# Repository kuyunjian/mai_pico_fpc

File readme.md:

.

.

.

.

.

# 1. 开源外壳适配的背板部分
.

.

.

.

.

.

.

.

.

.

## 这两个文件参考价格40-50元

## 安装指南如图
.

.

.

.

.

.

.

.

.

.

## t型螺母在匹配的方向可以直接盖到铝型材里
## 螺丝用m4L16 L17 L18都可以

## 还可以买M4L11或者L12或者L13的沉头螺丝（或者非沉头螺丝两个）安装侧边提手，有预留孔位
.

.

.

.

.

.

.

.

.

.

## 还可以买夹板螺母装背带挂钩，整个背板是13mm的，配套夹板螺母买外径5内4L12的八个，螺丝m4l4到m4l10之间八个，背带自己买适配的
.

.

.

.

.

.

.

.

.

.

# 2. pcb部分
- **Gerber_IO_Board_v3.1_2024-12-14.zip**（IO板）：使用嘉立创EDA制作，可以通过EDA券进行打样。
- **Gerber_Button_Board_2024-12-14.zip**（四个功能键板）：使用嘉立创EDA制作，可以通过EDA券进行打样。
- **Gerber_IO_Touch_Board_v3.0_5_2024-12-14.zip**（触摸板）：使用嘉立创EDA制作，可以通过EDA券进行打样。
- **fpc-button.zip**（按键板）：使用KiCad制作，在嘉立创下单助手中仅能用通用券进行打样。

---
分体板共四个pcb文件，均在 [JOZA-ORANGE](https://github.com/JOZA-ORANGE/mai_pico) 的基础上改进而来

## 更新说明：IO板
-增加了树莓派Pico对应的引脚丝印。  
  - 一侧仅焊接带标点的焊盘。  
  - 另一侧需要全部焊接。

- **读卡器焊盘**：更改为XH2.54接口。

- **按键PCB连接**：更改为12针0.5mm间距的FPC接口。

### 连接方式：
- IO板与按键PCB之间通过**反向连接**的FPC排线连接。
- 其他FPC排线连接均为**同向**连接。
- 按键板之间使用**40mm**的FPC排线进行连接。

---

## 螺丝孔
间距见图
IO板有两个4.1mm的螺丝孔，四个2mm的螺丝孔
.

.

.

.

.

.

.

.

.

.

  - 暂时没有固定方案，建议使用热熔胶将其固定在读卡器对面。

2024年12月29日可使用热压螺母加螺丝固定在一侧，夹具暂未更新到github，急需可以自己画，这里作为参考
.

.

.

.

.

.

.

.

.

.
触摸板有两个4.1mm的螺丝孔，封装宽度小于6mm，可以塞入欧标1515铝型材槽（6.1mm）
.

.

.

.

.

.

.

.

.

.

四个按键板有两个4.1mm的螺丝孔，受限于fpc座，无法将其放入槽内
.

.

.

.

.

.

.

.

.

.

按键板展示
.

.

.

.

.

.

.

.

.

.

---

## 关于该项目：

- 按键PCB与IO板通过12针FPC排线连接。
- 由于技术限制，PCB源文件未能与原理图建立连接。

### 未来更新内容：
- **更宽的按键帽**。
- 适配**分体主板**的**外壳**设计。
- 提供**组装建议**，方便安装。
- 其他**改进与优化**。

敬请期待更多精彩更新！

部分材料：
.

.

.

.

.

---
---
---
---
---
# Touch Panel and Function Key Boards

The **touch panel** and **four function key boards** can be found in **[JOZA-ORANGE's GitHub branch](https://github.com/JOZA-ORANGE/mai_pico)**.

## IO Board Modifications
The IO board includes the following updates:  
- Added **pin silkscreen** corresponding to the Raspberry Pi Pico.  
  - Only solder pads **with markers** on one side.  
  - Solder **all pads** on the other side.  
- Changed the **card reader pad** to an **XH2.54 connector**.  
- Updated the connection to the button PCB to a **12-pin 0.5mm pitch FPC connector**.  

### Connection Details
- The FPC cable between the IO board and the button PCB is **reversed**.  
- All other FPC connections are **same-direction**.  
- Button boards are connected using **40mm FPC cables**.

Visit the branch for more details and updates.

# About This Project

In this branch's shared link:  
- The **button PCB** is connected via a **12-pin FPC cable**.  
- **Technical limitations** prevent the PCB source file from linking to the schematic.  

## Future Updates
Potential updates may include:  
- **Wider button caps**.  
- **Enclosures** compatible with split mainboards.  
- **Assembly tips** for easier setup.  
- Additional **improvements and enhancements**.

Stay tuned for more exciting developments!

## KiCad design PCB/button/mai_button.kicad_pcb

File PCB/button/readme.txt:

这个kicad源文件非常不标准，是在原whowe的button基础上硬改的
这个button和分体io板用反向14p 0.5mmfpc排线连接
每两个button之间用同向14p fpc排线连接，长度40mm以上

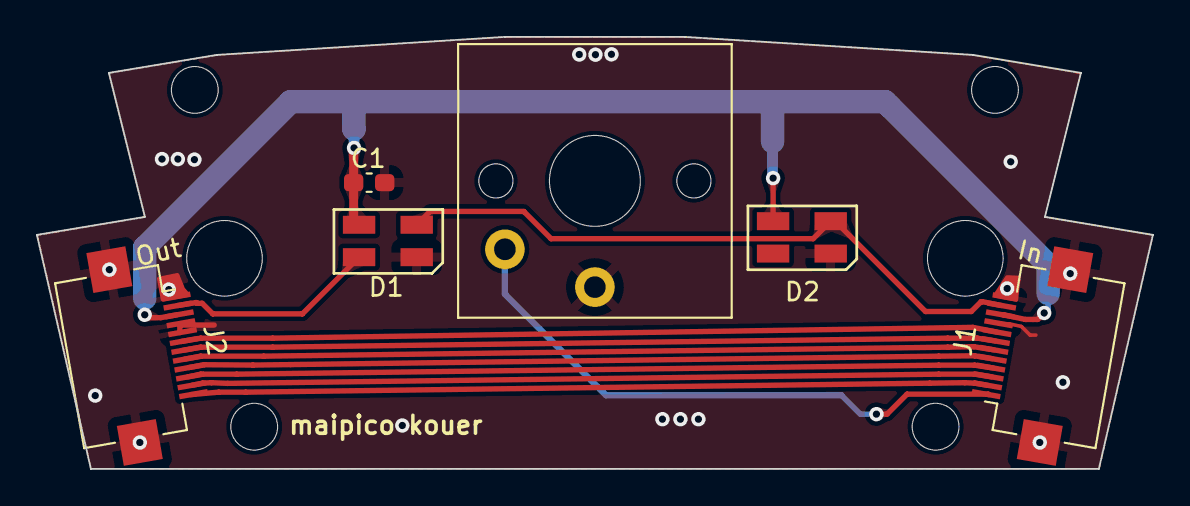
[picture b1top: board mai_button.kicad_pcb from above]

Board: 2 copper layers, 62.0 x 24.0 mm, 12 parts (0 on the bottom side), 12 nets.

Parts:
C1: 0.1uF; C_0603_1608Metric_Pad1.08x0.95mm_HandSolder
D1, D2: WS2812B_Unified; WS2812B-2835
J1, J2: Conn_01x14; Hirose_FH12-12S-0.5SH_1x12-1MP_P0.50mm_Horizontal_宽
SCR1, SCR2, SCR3, SCR4: ScrewHole; Hole2.5
SCR5, SCR6: ScrewHole; Hole4.0
SW1: SW_DIP_x01; SW_Kailh_Choc_V1V2_1.00u_LED

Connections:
+5V: C1.1, D1.V (VDD), D2.V (VDD), J1.10, J2.3
GND: C1.2, D1.G (VSS), D2.G (VSS), J1.9, J1.12, J1.MP, J2.1, J2.4, J2.5, J2.MP, SW1.1
unnamed: D1.I (In), D2.I (In), J1.11
unnamed: D1.O (Out), J2.2
unnamed: J1.1, SW1.2
unnamed: J1.2, J2.12
unnamed: J1.3, J2.11
unnamed: J1.4, J2.10
unnamed: J1.5, J2.9
unnamed: J1.6, J2.8
unnamed: J1.7, J2.7
unnamed: J1.8, J2.6

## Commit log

2024-12-08 Create pcb
2024-12-08 Create temp
2025-03-05 更新readme，上传参考图片
2025-03-08 更新readme
    2025年3月8日
2025-03-10 更新readme
2025-03-11 更新readme
    下次更新估计要几天之后了，休息一下
2025-03-11 emmm
